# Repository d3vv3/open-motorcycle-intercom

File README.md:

<p align="center">
    
    <br/>
    <b>Open Source Mesh and Bluetooth Motorcycle Intercom</b>
    <br/>
    <br/>
    <a href="https://openhelmet.devve.space">website</a> | <a href="https://discord.gg/XxBSnwSDst">discord</a>
</p>

OpenHelmet is an **open-source, motorcycle intercom system**
designed to outperform current proprietary solutions in **latency, scalability, transparency, and hackability**.

## Key goals

- Open protocol and open firmware
- Commodity, off-the-shelf hardware
- Use any microphone and any speakers from your existing helmet setup
- Mesh networking for 4-8+ riders
- Real-time full-duplex voice
- 8-16 hours of active riding per charge
- Bluetooth phone and media audio (calls, GPS, music, etc)
- Interoperability with legacy Bluetooth intercoms (Cardo, Sena, etc.) via standard profiles

This project explicitly avoids reverse-engineering proprietary intercom protocols.
Interoperability is achieved **only through standard Bluetooth audio profiles**.

---

## Why

- Cardo/Sena mesh protocols are proprietary and closed
- True mesh interoperability with and between them is impossible today
- Voice communication requires **deterministic latency**, not best-effort networking

As a result, OpenHelmet is designed around **custom real-time audio transport**.

---

## Roadmap

### Single-MCU

See [the wiring guide](docs/wiring.md) for the ESP32-S31 Function CoreBoard-1.

- [x] **ESP32-S31 Function CoreBoard-1** with 16 MB flash and 16 MB PSRAM
- [x] Onboard ES8311 capture/codec and NS4150B/J9 output
- [x] TDMA mesh protocol over [ESP-NOW](https://www.espressif.com/en/solutions/low-power-solutions/esp-now) (2.4 GHz)
- [x] LC3 low-bitrate voice
- [x] Classic Bluetooth A2DP sink, AVRCP, and HFP HF client
- [x] VOX for voice activation
- [x] Configure ESP32 tx power to 20 dBm (100 mW) for ESP-NOW
- [x] Silence suppression - most silent audio frames are suppressed; control traffic and occasional comfort updates remain
- [x] Receive mixing with first-speaker retention; a new active source can replace the longest-silent source after 400 ms

Limitations:
- ESP-NOW is not interoperable with nRF52 ESB.
- The ESP-NOW and Bluetooth stacks share the same radio, so mesh and Bluetooth are mutually exclusive: turning mesh on turns Bluetooth off.

### Dual-MCU

Development and validation only. Check [the wiring guide](docs/wiring.md) for
the S31/nRF52840 SPI wiring.

The nRF52840 firmware uses the radio's +8 dBm output directly.
An nRF21540 is needed for additional range, efficiency and antenna radio distribution. See "Custom PCB" section below.

> The nRF21540 is needed for actual range improvements.
> The nRF52840 alone is not a range improvement over the ESP32-S31.

- [x] **ESP32-S31 + Nordic nRF52840**
- [x] TDMA mesh protocol over [ESB](https://docs.nordicsemi.com/bundle/ncs-latest/page/nrf/protocols/esb/index.html) radio with custom PHY control
  > ESB is configured for 2 Mbps with +8 dBm TX power
- [x] SPI audio & control bridge between MCUs
  > The nRF52840 is the SPI master and polls the ESP32 bridge every 2 ms.
- [x] Noise suppression path
- [ ] Allow user to choose between [ESP-NOW](https://www.espressif.com/en/solutions/low-power-solutions/esp-now) and [ESB](https://docs.nordicsemi.com/bundle/ncs-latest/page/nrf/protocols/esb/index.html)
  > ESP-NOW is not interoperable with nRF52 ESB. The firmware currently selects ESB when the bridge is detected and otherwise falls back to ESP-NOW; comparative range, power, and latency remain to be measured.
- [x] Relay grants limited to at most two active speakers
- [x] Three-source receive mixer with first-speaker retention and 400 ms silent-source eviction
- [x] Silence suppression - most silent audio frames are suppressed; control traffic and occasional comfort updates remain
- [x] Bluetooth media playback (music, GPS, etc.) during mesh operation.

### Custom PCB

- [x] Schematic
- [ ] PCB layout
- [x] Include [nRF21540 RF FEM](https://www.nordicsemi.com/Products/nRF21540) in the schematics and PCB design

See the [wiring guide](docs/wiring.md) for the current assembled prototype.

### Ongoing

- [x] Mute mesh during phone call; resume mesh after call ends
- [x] Mesh channels with RGB LED channel indicator by color (e.g. green=1, red=2, blue=3, etc.)
- [x] Buttons for channel selection, volume, mesh toggle, and Bluetooth pairing
- [x] Multi-hop mesh
- [x] Replace beeps with voice prompts for button operations
- [x] Hold prompts: holding a button announces what releasing it will do (mesh on/off, phone pairing, next channel)
- [x] Phone connect and disconnect beeps, and a "Phone paired" prompt after a new pairing
- [x] ESP-NOW mesh and Bluetooth take turns on the shared radio: mesh on turns Bluetooth off, mesh off turns it back on and reconnects the phone
- [ ] Power budgeting and optimization for 8-16 hours of active riding per charge
- [ ] Testing on real motorcycle rides
- [ ] E2EE

---

## Transport Protocol Design

### Why Not Bluetooth Mesh / BLE Audio

- High latency
- Unpredictable scheduling
- Poor scaling for continuous audio

These technologies are unsuitable for real-time group voice.

---

## Custom Mesh Strategy

### Scheduled Voice and Control

OpenHelmet divides each 20 ms TDMA frame into scheduled voice slots and a control window:

- **TDMA** for mesh audio packets
- A rotating owner for joined-node control traffic; coordinator SYNC frames have a reserved window
- Bounded randomized contention for unjoined ESP-NOW JOIN requests

#### TDMA (Voice)

Each current mesh audio payload represents 20 ms of sound: two 10 ms LC3 frames, encoded as 24 bytes each. These 48 bytes travel together in one packet, not in separate TDMA slots.

On the nRF transport, a bundle can also carry previous audio frames for loss recovery. This increases packet size without changing the 20 ms transmission cadence.

- Fixed time slots per node
- One bounded transmission opportunity per node per 20 ms TDMA frame
- Deadline checks reject work that is already late; they do not guarantee exact RF completion timing

Configured frame structure (20 ms frame, up to 8 nodes; durations include guard time):

```
| Slot 1 | Slot 2 | Slot 3 | ... | Slot 8 | Control | Margin |
|  2 ms  |  2 ms  |  2 ms  | ... |  2 ms  |   2 ms  |  2 ms |
```

- Voice slots: 8 × 2 ms = 16 ms
- Control window: 2 ms (scheduled sync/topology/status traffic)
- Frame margin: 2 ms
- Voice and control deadlines reserve the last 500 µs of each nominal 2 ms window, leaving 1.5 ms before the deadline

VOX suppresses local LC3 encoding and audio transmission during silence, after its hangover period. Capture and voice detection continue. The TDMA schedule remains unchanged, and synchronization, keepalives, and required relay/control traffic continue.

Motorcycle groups are small and topology changes slowly, making TDMA practical.

#### Control

Used for:
- Joining/leaving the group
- Topology updates
- Slot maps and synchronization

Joined-node control packets use a bounded queue and scheduled ownership. Unassigned ESP-NOW JOIN requests use a minimum interval plus randomized jitter. These rules reduce contention, but they do not guarantee collision-free RF operation.

---

## Quick Start

For published paired flash bundles and the alpha/stable release process, see
[Firmware releases](docs/releases.md).

### Prerequisites

- [ESP-IDF v6.1 preview](https://docs.espressif.com/projects/esp-idf/en/release-v6.1/esp32s31/get-started/)
- [ESP32-S31 Function CoreBoard-1](https://docs.espressif.com/projects/esp-idf/en/release-v6.1/esp32s31/get-started/) with 16 MB flash and 16 MB PSRAM
- ESP32-S31 support in ESP-IDF v6.1 is preview
- CI pins a tested ESP-IDF image that includes the upstream S31 Bluetooth
  sniff-subrate fix. The mutable `v6.1` tag does not contain that fix.
- (Optional) XIAO nRF52840
- USB-C data cables
- [Development environment and ESP32 setup](docs/getting_started.md)
- [Audio and dual-MCU wiring guide](docs/wiring.md)
- (Optional) [KiCad](https://www.kicad.org/)

### Build

```bash
# Optional local environment example (path is machine-specific; this installation
# may use the unpatched v6.1 image and does not include the S31 sniff-subrate fix)
source "$HOME/.espressif/tools/activate_idf_v6.1.sh"

# Select the ESP32-S31 preview target
idf.py --preview set-target esp32s31

# Build firmware
idf.py build
```

For the tested SDK image with the tested fix, use the same immutable image as CI
instead of a local v6.1 installation:

```bash
docker run --rm --user "$(id -u):$(id -g)" -e HOME=/tmp \
  -v "$PWD:/project" -w /project \
  espressif/idf@sha256:8ac794c57fd4cac246cb8d2ada4002fa26337ac7df683047b5b83743dbedb6b7 \
  bash -lc 'idf.py --preview set-target esp32s31 && idf.py build'
```

That image reports ESP-IDF commit `9a97f6c54ec638111ce55cd36581b3c192f15207`
and S31 Bluetooth binary commit `3d8cee57c4ccff603d4f52fe16be1f04ece78ede`;
the latter includes the upstream sniff-subrate fix. The stable `espressif/idf:v6.1`
tag does not include this fix. A delayed BOOT guard alone does not fix
phone-originated transitions: cooldown handling and the external Bluetooth
controller fix are also required.

For the optional XIAO nRF52840 firmware, build the Rust crate with its pinned toolchain and convert it to UF2
(see [getting started](docs/getting_started.md#build-the-nrf-firmware)):

```bash
(cd rust/nrf-embassy-firmware &&
  cargo build --locked --release --target thumbv7em-none-eabihf)

python3 tools/migration/nrf_proof.py \
  rust/nrf-embassy-firmware/target/thumbv7em-none-eabihf/release/nrf-embassy-firmware \
  rust/nrf-embassy-firmware/target/thumbv7em-none-eabihf/release/nrf-embassy-firmware.uf2
```

### Recovery and Flashing

```bash
# Find your serial port
ls /dev/ttyACM* /dev/ttyUSB*

# Native USB JTAG/OpenOCD with board/esp32s31-builtin.cfg is the validated
# recovery path on the current setup. Serial flashing has proved unreliable here.
```

### Monitor Serial Output

```bash
# Option 1: Using idf.py (interactive, requires TTY)
idf.py -p /dev/ttyACM0 monitor

# Option 2: Using stty + cat (non-interactive)
stty -F /dev/ttyACM0 115200 raw -echo && cat /dev/ttyACM0
```

**Exit monitor:** `Ctrl+]`

### Expected Boot Log

```
I (xxx) omi: ========================================
I (xxx) omi: OMI - Open Motorcycle Intercom
I (xxx) omi: Phase 2: Single-Hop RF Link
I (xxx) omi: ========================================
I (xxx) omi: Boot time: <milliseconds> ms
I (xxx) omi: IDF version: v6.1
I (xxx) omi: Free heap: <bytes> bytes
I (xxx) omi: ========================================
I (xxx) omi: nRF52840 not detected - using ESP-NOW transport
I (xxx) omi: Mesh networking ready (desired state: disabled)
I (xxx) omi: System running!
```

### Troubleshooting

| Issue | Solution |
|-------|----------|
| Device not found | Use a data cable (not charge-only), try different USB port |
| Garbage characters in monitor | Wrong baud rate, use 115200 |

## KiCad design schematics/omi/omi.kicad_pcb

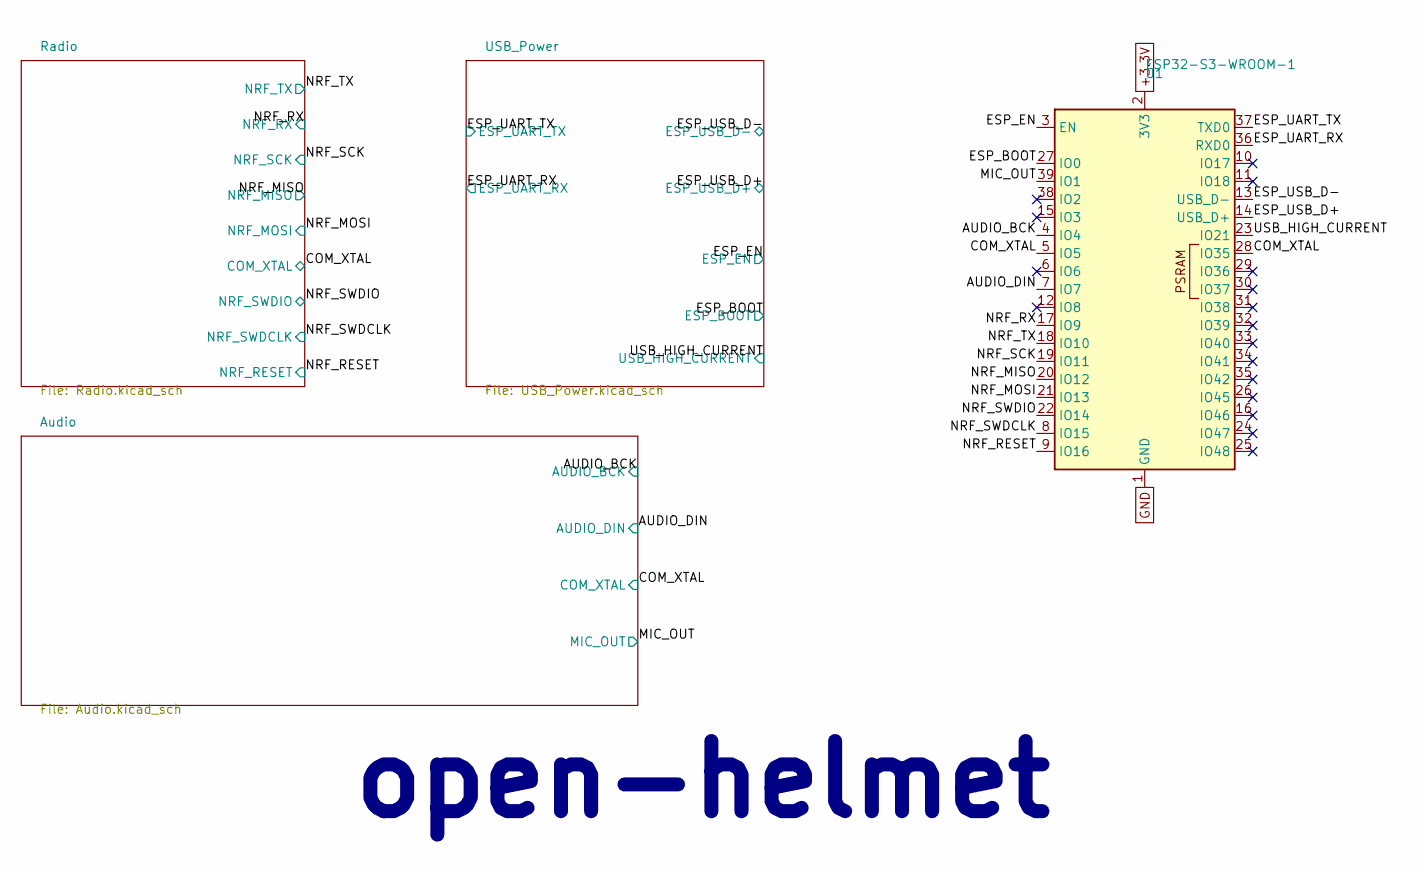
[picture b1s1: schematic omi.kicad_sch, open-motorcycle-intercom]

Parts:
U1: ESP32-S3-WROOM-1; MNF PART NUMBER ESP32-S3-WROOM-1-N8; LCSC C2913198

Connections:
+3.3V: U1.2 (3V3); also elsewhere on the board
/AUDIO_BCK: U1.4 (IO4); also elsewhere on the board
/AUDIO_DIN: U1.7 (IO7); also elsewhere on the board
/COM_XTAL: U1.5 (IO5), U1.28 (IO35); also elsewhere on the board
/ESP_BOOT: U1.27 (IO0); also elsewhere on the board
/ESP_EN: U1.3 (EN); also elsewhere on the board
/ESP_UART_RX: U1.36 (RXD0); also elsewhere on the board
/ESP_UART_TX: U1.37 (TXD0); also elsewhere on the board
/ESP_USB_D+: U1.14 (USB_D+); also elsewhere on the board
/ESP_USB_D-: U1.13 (USB_D-); also elsewhere on the board
/MIC_OUT: U1.39 (IO1); also elsewhere on the board
/NRF_MISO: U1.20 (IO12); also elsewhere on the board
/NRF_MOSI: U1.21 (IO13); also elsewhere on the board
/NRF_RESET: U1.9 (IO16); also elsewhere on the board
/NRF_RX: U1.17 (IO9); also elsewhere on the board
/NRF_SCK: U1.19 (IO11); also elsewhere on the board
/NRF_SWDCLK: U1.8 (IO15); also elsewhere on the board
/NRF_SWDIO: U1.22 (IO14); also elsewhere on the board
/NRF_TX: U1.18 (IO10); also elsewhere on the board
/USB_HIGH_CURRENT: U1.23 (IO21); also elsewhere on the board
GND: U1.1 (GND), U1.40 (GND), U1.41 (GND); also elsewhere on the board

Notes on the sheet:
open-helmet

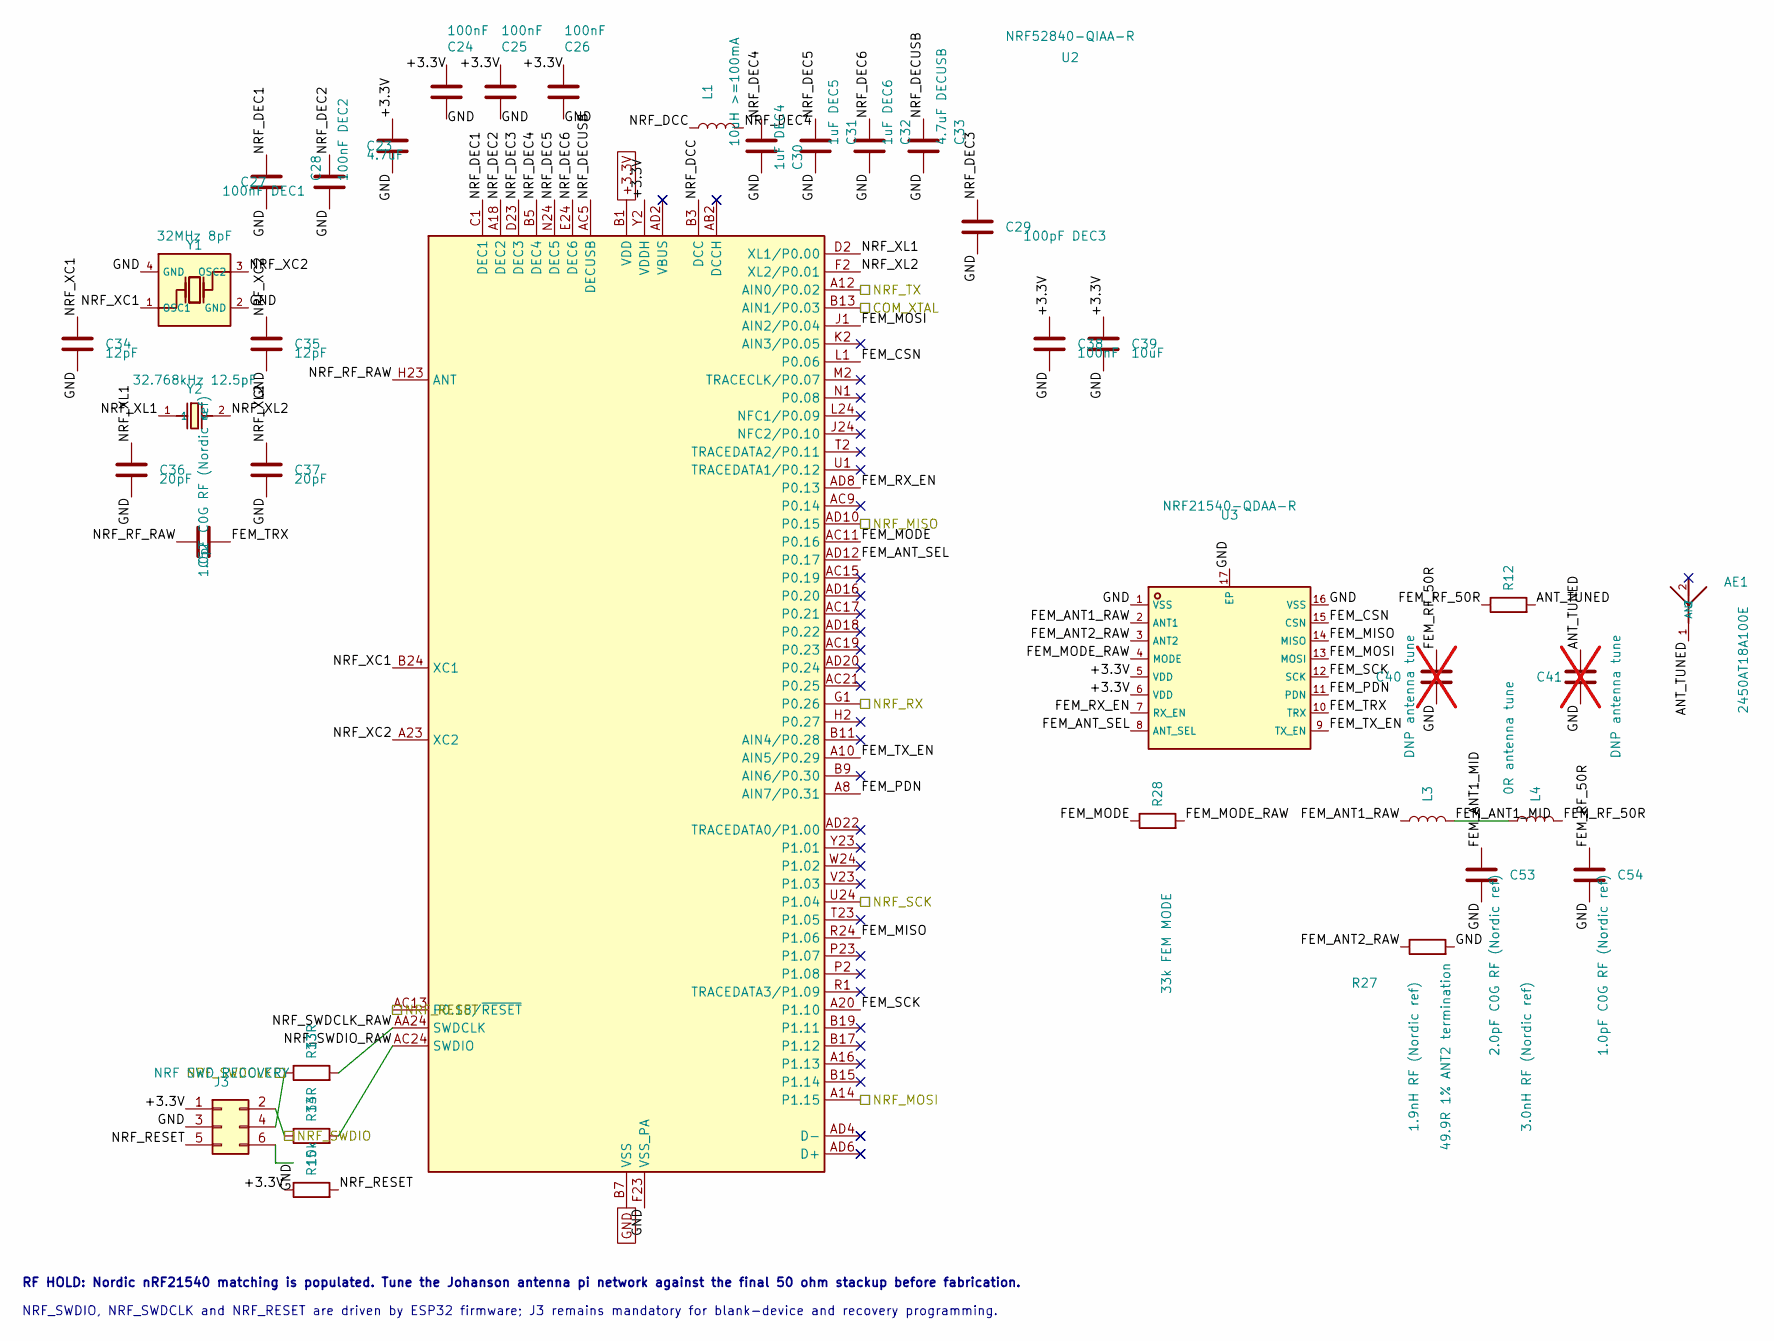
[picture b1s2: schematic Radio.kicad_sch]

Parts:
AE1: 2450AT18A100E; ANT-SMD_L3.2-W1.6; MNF PART NUMBER 2450AT18A100E; LCSC C89334
C23: 4.7uF; C_0805_2012Metric; MNF PART NUMBER C2012X7R1A475KT000N; LCSC C76639
C24, C25, C26, C38: 100nF; C_0603_1608Metric; MNF PART NUMBER CC0603KRX7R7BB104; LCSC C108079
C27: 100nF DEC1; C_0603_1608Metric; MNF PART NUMBER CC0603KRX7R7BB104; LCSC C108079
C28: 100nF DEC2; C_0603_1608Metric; MNF PART NUMBER CC0603KRX7R7BB104; LCSC C108079
C29: 100pF DEC3; C_0603_1608Metric; MNF PART NUMBER CC0603JRNPO9BN101; LCSC C14665
C30: 1uF DEC4; C_0603_1608Metric; MNF PART NUMBER CC0603KRX7R6BB105; LCSC C113807
C31: 1uF DEC5; C_0603_1608Metric; MNF PART NUMBER CC0603KRX7R6BB105; LCSC C113807
C32: 1uF DEC6; C_0603_1608Metric; MNF PART NUMBER CC0603KRX7R6BB105; LCSC C113807
C33: 4.7uF DECUSB; C_0805_2012Metric; MNF PART NUMBER C2012X7R1A475KT000N; LCSC C76639
C34, C35: 12pF; C_0603_1608Metric; MNF PART NUMBER CC0603JRNPO9BN120; LCSC C107034
C36, C37: 20pF; C_0603_1608Metric; MNF PART NUMBER CC0603GRNPO9BN200; LCSC C325469
C39: 10uF; C_0805_2012Metric; Voltage 10V; MNF PART NUMBER TCC0805X5R106K100FT; LCSC C380331
C40, C41: DNP antenna tune; C_0201_0603Metric; not fitted
C52, C54: 1.0pF C0G RF (Nordic ref); C_0201_0603Metric; MNF PART NUMBER GRM0335C1H1R0BA01D; LCSC C85893
C53: 2.0pF C0G RF (Nordic ref); C_0201_0603Metric; MNF PART NUMBER GJM0335C1E2R0BB01D; LCSC C88875
J3: NRF SWD RECOVERY; Tag-Connect_TC2030-IDC-NL_2x03_P1.27mm_Vertical; MNF PART NUMBER TC2030-IDC-NL; LCSC Not stocked - factory fixture
L1: 10uH >=100mA; L_0603_1608Metric; MNF PART NUMBER LQM18DN100M70L; LCSC C713281
L3: 1.9nH RF (Nordic ref); L_0201_0603Metric; MNF PART NUMBER LQP03TN1N9B02D; LCSC C206445
L4: 3.0nH RF (Nordic ref); L_0201_0603Metric; MNF PART NUMBER LQP03TN3N0B02D; LCSC C98044
R12: 0R antenna tune; R_0201_0603Metric; MNF PART NUMBER RC0201JR-070RL; LCSC C106228
R13, R14: 33R; R_0603_1608Metric; MNF PART NUMBER 0603WAF330JT5E; LCSC C23140
R15: 10k; R_0603_1608Metric; MNF PART NUMBER 0603WAF1002T5E; LCSC C25804
R27: 49.9R 1% ANT2 termination; R_0201_0603Metric; MNF PART NUMBER RC0201FR-0749R9L; LCSC C155744
R28: 33k FEM MODE; R_0603_1608Metric; MNF PART NUMBER 0603WAF3302T5E; LCSC C4216
U2: NRF52840-QIAA-R; AQFN-73_L7.0-W7.0-P0.50-BL-EP4.8; MNF PART NUMBER NRF52840-QIAA-R; LCSC C190794
U3: NRF21540-QDAA-R; QFN-16_L4.0-W4.0-P0.65-BL-EP2.7; MNF PART NUMBER NRF21540-QDAA-R; LCSC C1518188
Y1: 32MHz 8pF; CRYSTAL-SMD_4P-L3.2-W2.5-BL; MNF PART NUMBER S3232000081040; LCSC C426985
Y2: 32.768kHz 12.5pF; OSC-SMD_L3.2-W1.5; MNF PART NUMBER SC-32S32.768kHz20PPM12.5pF; LCSC C97606

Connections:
+3.3V: C23.1, C24.1, C25.1, C26.1, C38.1, C39.1, J3.1, R15.1, U2.A22 (VDD), U2.AD14 (VDD), U2.AD23 (VDD), U2.B1 (VDD), U2.W1 (VDD), U2.Y2 (VDDH), U3.5 (VDD), U3.6 (VDD); also elsewhere on the board
/COM_XTAL: U2.B13 (AIN1/P0.03); also elsewhere on the board
/NRF_MISO: U2.AD10 (P0.15); also elsewhere on the board
/NRF_MOSI: U2.A14 (P1.15); also elsewhere on the board
/NRF_RESET: J3.5, R15.2, U2.AC13 (P0.18/~RESET); also elsewhere on the board
/NRF_RX: U2.G1 (P0.26); also elsewhere on the board
/NRF_SCK: U2.U24 (P1.04); also elsewhere on the board
/NRF_SWDCLK: J3.4, R13.1; also elsewhere on the board
/NRF_SWDIO: J3.2, R14.1; also elsewhere on the board
/NRF_TX: U2.A12 (AIN0/P0.02); also elsewhere on the board
/Radio/ANT_TUNED: AE1.1 (ANT_1), C41.1, R12.2
/Radio/FEM_ANT1_MID: C53.1, L3.2, L4.1
/Radio/FEM_ANT1_RAW: L3.1, U3.2 (ANT1)
/Radio/FEM_ANT2_RAW: R27.1, U3.3 (ANT2)
/Radio/FEM_ANT_SEL: U2.AD12 (P0.17), U3.8 (ANT_SEL)
/Radio/FEM_CSN: U2.L1 (P0.06), U3.15 (CSN)
/Radio/FEM_MISO: U2.R24 (P1.06), U3.14 (MISO)
/Radio/FEM_MODE: R28.1, U2.AC11 (P0.16)
/Radio/FEM_MODE_RAW: R28.2, U3.4 (MODE)
/Radio/FEM_MOSI: U2.J1 (AIN2/P0.04), U3.13 (MOSI)
/Radio/FEM_PDN: U2.A8 (AIN7/P0.31), U3.11 (PDN)
/Radio/FEM_RF_50R: C40.1, C54.1, L4.2, R12.1
/Radio/FEM_RX_EN: U2.AD8 (P0.13), U3.7 (RX_EN)
/Radio/FEM_SCK: U2.A20 (P1.10), U3.12 (SCK)
/Radio/FEM_TRX: C52.2, U3.10 (TRX)
/Radio/FEM_TX_EN: U2.A10 (AIN5/P0.29), U3.9 (TX_EN)
/Radio/NRF_DCC: L1.1, U2.B3 (DCC)
/Radio/NRF_DEC1: C27.1, U2.C1 (DEC1)
/Radio/NRF_DEC2: C28.1, U2.A18 (DEC2)
/Radio/NRF_DEC3: C29.1, U2.D23 (DEC3)
/Radio/NRF_DEC4: C30.1, L1.2, U2.B5 (DEC4)
/Radio/NRF_DEC5: C31.1, U2.N24 (DEC5)
/Radio/NRF_DEC6: C32.1, U2.E24 (DEC6)
/Radio/NRF_DECUSB: C33.1, U2.AC5 (DECUSB)
/Radio/NRF_RF_RAW: C52.1, U2.H23 (ANT)
/Radio/NRF_SWDCLK_RAW: R13.2, U2.AA24 (SWDCLK)
/Radio/NRF_SWDIO_RAW: R14.2, U2.AC24 (SWDIO)
/Radio/NRF_XC1: C34.1, U2.B24 (XC1), Y1.1 (OSC1)
/Radio/NRF_XC2: C35.1, U2.A23 (XC2), Y1.3 (OSC2)
/Radio/NRF_XL1: C36.1, U2.D2 (XL1/P0.00), Y2.1
/Radio/NRF_XL2: C37.1, U2.F2 (XL2/P0.01), Y2.2
GND: C23.2, C24.2, C25.2, C26.2, C27.2, C28.2, C29.2, C30.2, C31.2, C32.2, C33.2, C34.2, C35.2, C36.2, C37.2, C38.2, C39.2, C40.2, C41.2, C53.2, C54.2, J3.3, J3.6, R27.2, U2.B7 (VSS), U2.EP (VSS), U2.F23 (VSS_PA), U3.1 (VSS), U3.16 (VSS), U3.17 (EP), Y1.2 (GND), Y1.4 (GND); also elsewhere on the board

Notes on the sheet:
RF HOLD: Nordic nRF21540 matching is populated. Tune the Johanson antenna pi network against the final 50 ohm stackup before fabrication.
NRF_SWDIO, NRF_SWDCLK and NRF_RESET are driven by ESP32 firmware; J3 remains mandatory for blank-device and recovery programming.

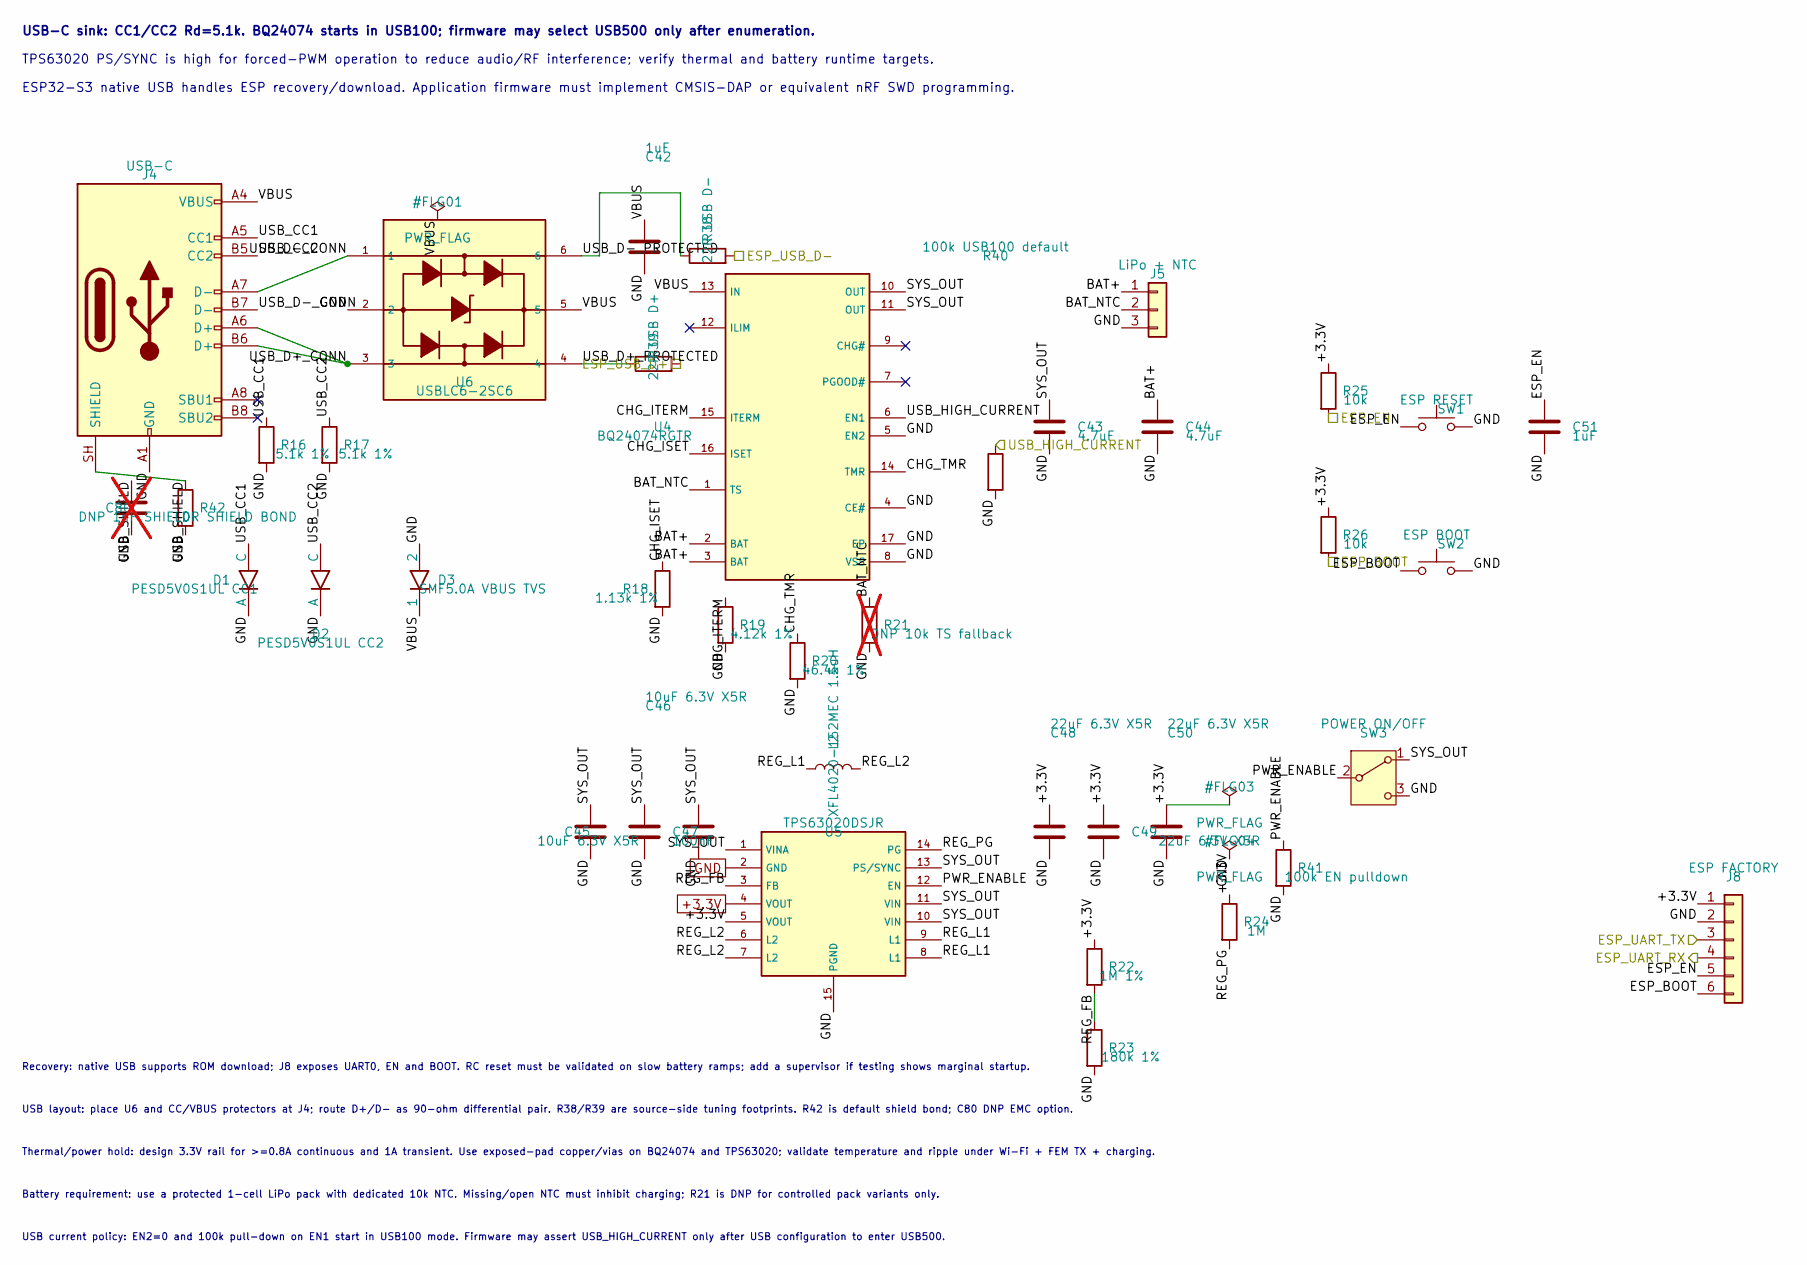
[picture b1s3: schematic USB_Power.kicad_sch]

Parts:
C42, C51: 1uF; C_0603_1608Metric; MNF PART NUMBER CC0603KRX7R6BB105; LCSC C113807
C43, C44: 4.7uF; C_0805_2012Metric; MNF PART NUMBER C2012X7R1A475KT000N; LCSC C76639
C45, C46: 10uF 6.3V X5R; C_0805_2012Metric; MNF PART NUMBER TCC0805X5R106K100FT; LCSC C380331
C47: 100nF; C_0603_1608Metric; MNF PART NUMBER CC0603KRX7R7BB104; LCSC C108079
C48, C49, C50: 22uF 6.3V X5R; C_0805_2012Metric; MNF PART NUMBER TCC0805X5R226K100FT; LCSC C380336
C80: DNP 1nF SHIELD; C_0603_1608Metric; MNF PART NUMBER TBD EMC tuning; not fitted
D1: PESD5V0S1UL CC1; SOD-882_L1.0-W0.6-RD; MNF PART NUMBER PESD5V0S1UL,315; LCSC C85402
D2: PESD5V0S1UL CC2; SOD-882_L1.0-W0.6-RD; MNF PART NUMBER PESD5V0S1UL,315; LCSC C85402
D3: SMF5.0A VBUS TVS; SOD-123F_L2.8-W1.8-LS3.7-RD; MNF PART NUMBER SMF5.0A; LCSC C151296
J4: USB-C; USB_C_Receptacle_HRO_TYPE-C-31-M-12; MNF PART NUMBER TYPE-C-31-M-12; LCSC C165948
J5: LiPo + NTC; JST_GH_BM03B-GHS-TBT_1x03-1MP_P1.25mm_Vertical; MNF PART NUMBER BM03B-GHS-TBT(LF)(SN); LCSC C161691
J8: ESP FACTORY; PinHeader_1x06_P2.54mm_Vertical; MNF PART NUMBER PZ254V-11-06P; LCSC C492405
L2: XFL4020-152MEC 1.5uH; IND-SMD_L4.0-W4.0-A; MNF PART NUMBER XFL4020-152MEC; LCSC C3033018
R16, R17: 5.1k 1%; R_0603_1608Metric; MNF PART NUMBER 0603WAF5101T5E; LCSC C23186
R18: 1.13k 1%; R_0603_1608Metric; MNF PART NUMBER 0603WAF1131T5E; LCSC C22833
R19: 4.12k 1%; R_0603_1608Metric; MNF PART NUMBER 0603WAF4121T5E; LCSC C23041
R20: 46.4k 1%; R_0603_1608Metric; MNF PART NUMBER 0603WAF4642T5E; LCSC C23059
R21: DNP 10k TS fallback; R_0603_1608Metric; MNF PART NUMBER 0603WAF1002T5E; LCSC C25804; not fitted
R22: 1M 1%; R_0603_1608Metric; MNF PART NUMBER 0603WAF1004T5E; LCSC C22935
R23: 180k 1%; R_0603_1608Metric; MNF PART NUMBER 0603WAF1803T5E; LCSC C22827
R24: 1M; R_0603_1608Metric; MNF PART NUMBER 0603WAF1004T5E; LCSC C22935
R25, R26: 10k; R_0603_1608Metric; MNF PART NUMBER 0603WAF1002T5E; LCSC C25804
R38: 22R USB D-; R_0603_1608Metric; MNF PART NUMBER 0603WAF220JT5E; LCSC C23345
R39: 22R USB D+; R_0603_1608Metric; MNF PART NUMBER 0603WAF220JT5E; LCSC C23345
R40: 100k USB100 default; R_0603_1608Metric; MNF PART NUMBER 0603WAF1003T5E; LCSC C25803
R41: 100k EN pulldown; R_0603_1608Metric; MNF PART NUMBER 0603WAF1003T5E; LCSC C25803
R42: 0R SHIELD BOND; R_0603_1608Metric; MNF PART NUMBER 0603WAF0000T5E; LCSC C21189
SW1: ESP RESET; SW_Push_1P1T_XKB_TS-1187A; MNF PART NUMBER TS-1187A-B-A-B; LCSC C318884
SW2: ESP BOOT; SW_Push_1P1T_XKB_TS-1187A; MNF PART NUMBER TS-1187A-B-A-B; LCSC C318884
SW3: POWER ON/OFF; SW_SPDT_Shouhan_MSK12C02; MNF PART NUMBER MSK12C02; LCSC C431540
U4: BQ24074RGTR; QFN-16_L3.0-W3.0-P0.50-TL-EP1.7; MNF PART NUMBER BQ24074RGTR; LCSC C54313
U5: TPS63020DSJR; VSON-14_L4.0-W3.0-P0.50-BL-EP_TI_DSJ; MNF PART NUMBER TPS63020DSJR; LCSC C15483
U6: USBLC6-2SC6; SOT-23-6_L2.9-W1.6-P0.95-LS2.8-BL; MNF PART NUMBER TYPE-C-31-M-12; LCSC C7519

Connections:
+3.3V: C48.1, C49.1, C50.1, J8.1, R22.1, R24.1, R25.1, R26.1, U5.4 (VOUT), U5.5 (VOUT); also elsewhere on the board
/ESP_BOOT: J8.6, R26.2, SW2.1; also elsewhere on the board
/ESP_EN: C51.1, J8.5, R25.2, SW1.1; also elsewhere on the board
/ESP_UART_RX: J8.4; also elsewhere on the board
/ESP_UART_TX: J8.3; also elsewhere on the board
/ESP_USB_D+: R39.2; also elsewhere on the board
/ESP_USB_D-: R38.2; also elsewhere on the board
/USB_HIGH_CURRENT: R40.1, U4.6 (EN1); also elsewhere on the board
/USB_Power/BAT+: C44.1, J5.1, U4.2 (BAT), U4.3 (BAT)
/USB_Power/BAT_NTC: J5.2, R21.1, U4.1 (TS)
/USB_Power/CHG_ISET: R18.1, U4.16 (ISET)
/USB_Power/CHG_ITERM: R19.1, U4.15 (ITERM)
/USB_Power/CHG_TMR: R20.1, U4.14 (TMR)
/USB_Power/PWR_ENABLE: R41.1, SW3.2 (B), U5.12 (EN)
/USB_Power/REG_FB: R22.2, R23.1, U5.3 (FB)
/USB_Power/REG_L1: L2.1, U5.8 (L1), U5.9 (L1)
/USB_Power/REG_L2: L2.2, U5.6 (L2), U5.7 (L2)
/USB_Power/REG_PG: R24.2, U5.14 (PG)
/USB_Power/SYS_OUT: C43.1, C45.1, C46.1, C47.1, SW3.1 (A), U4.10 (OUT), U4.11 (OUT), U5.1 (VINA), U5.10 (VIN), U5.11 (VIN), U5.13 (PS/SYNC)
/USB_Power/USB_CC1: D1.1 (C), J4.A5 (CC1), R16.1
/USB_Power/USB_CC2: D2.1 (C), J4.B5 (CC2), R17.1
/USB_Power/USB_D+_CONN: J4.A6 (D+), J4.B6 (D+), U6.3
/USB_Power/USB_D+_PROTECTED: R39.1, U6.4
/USB_Power/USB_D-_CONN: J4.A7 (D-), J4.B7 (D-), U6.1
/USB_Power/USB_D-_PROTECTED: R38.1, U6.6
/USB_Power/USB_SHIELD: C80.1, J4.SH (SHIELD), R42.1
/USB_Power/VBUS: C42.1, D3.1, J4.A4 (VBUS), J4.A9 (VBUS), J4.B4 (VBUS), J4.B9 (VBUS), U4.13 (IN), U6.5
GND: C42.2, C43.2, C44.2, C45.2, C46.2, C47.2, C48.2, C49.2, C50.2, C51.2, C80.2, D1.2 (A), D2.2 (A), D3.2, J4.A1 (GND), J4.A12 (GND), J4.B1 (GND), J4.B12 (GND), J5.3, J8.2, R16.2, R17.2, R18.2, R19.2, R20.2, R21.2, R23.2, R40.2, R41.2, R42.2, SW1.2, SW2.2, SW3.3 (C), U4.4 (CE#), U4.5 (EN2), U4.8 (VSS), U4.17 (EP), U5.2 (GND), U5.15 (PGND), U6.2; also elsewhere on the board

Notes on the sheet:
USB-C sink: CC1/CC2 Rd=5.1k. BQ24074 starts in USB100; firmware may select USB500 only after enumeration.
TPS63020 PS/SYNC is high for forced-PWM operation to reduce audio/RF interference; verify thermal and battery runtime targets.
ESP32-S3 native USB handles ESP recovery/download. Application firmware must implement CMSIS-DAP or equivalent nRF SWD programming.
USB current policy: EN2=0 and 100k pull-down on EN1 start in USB100 mode. Firmware may assert USB_HIGH_CURRENT only after USB configuration to enter USB500.
Battery requirement: use a protected 1-cell LiPo pack with dedicated 10k NTC. Missing/open NTC must inhibit charging; R21 is DNP for controlled pack variants only.
Thermal/power hold: design 3.3V rail for >=0.8A continuous and 1A transient. Use exposed-pad copper/vias on BQ24074 and TPS63020; validate temperature and ripple under Wi-Fi + FEM TX + charging.
USB layout: place U6 and CC/VBUS protectors at J4; route D+/D- as 90-ohm differential pair. R38/R39 are source-side tuning footprints. R42 is default shield bond; C80 DNP EMC option.
Recovery: native USB supports ROM download; J8 exposes UART0, EN and BOOT. RC reset must be validated on slow battery ramps; add a supervisor if testing shows marginal startup.

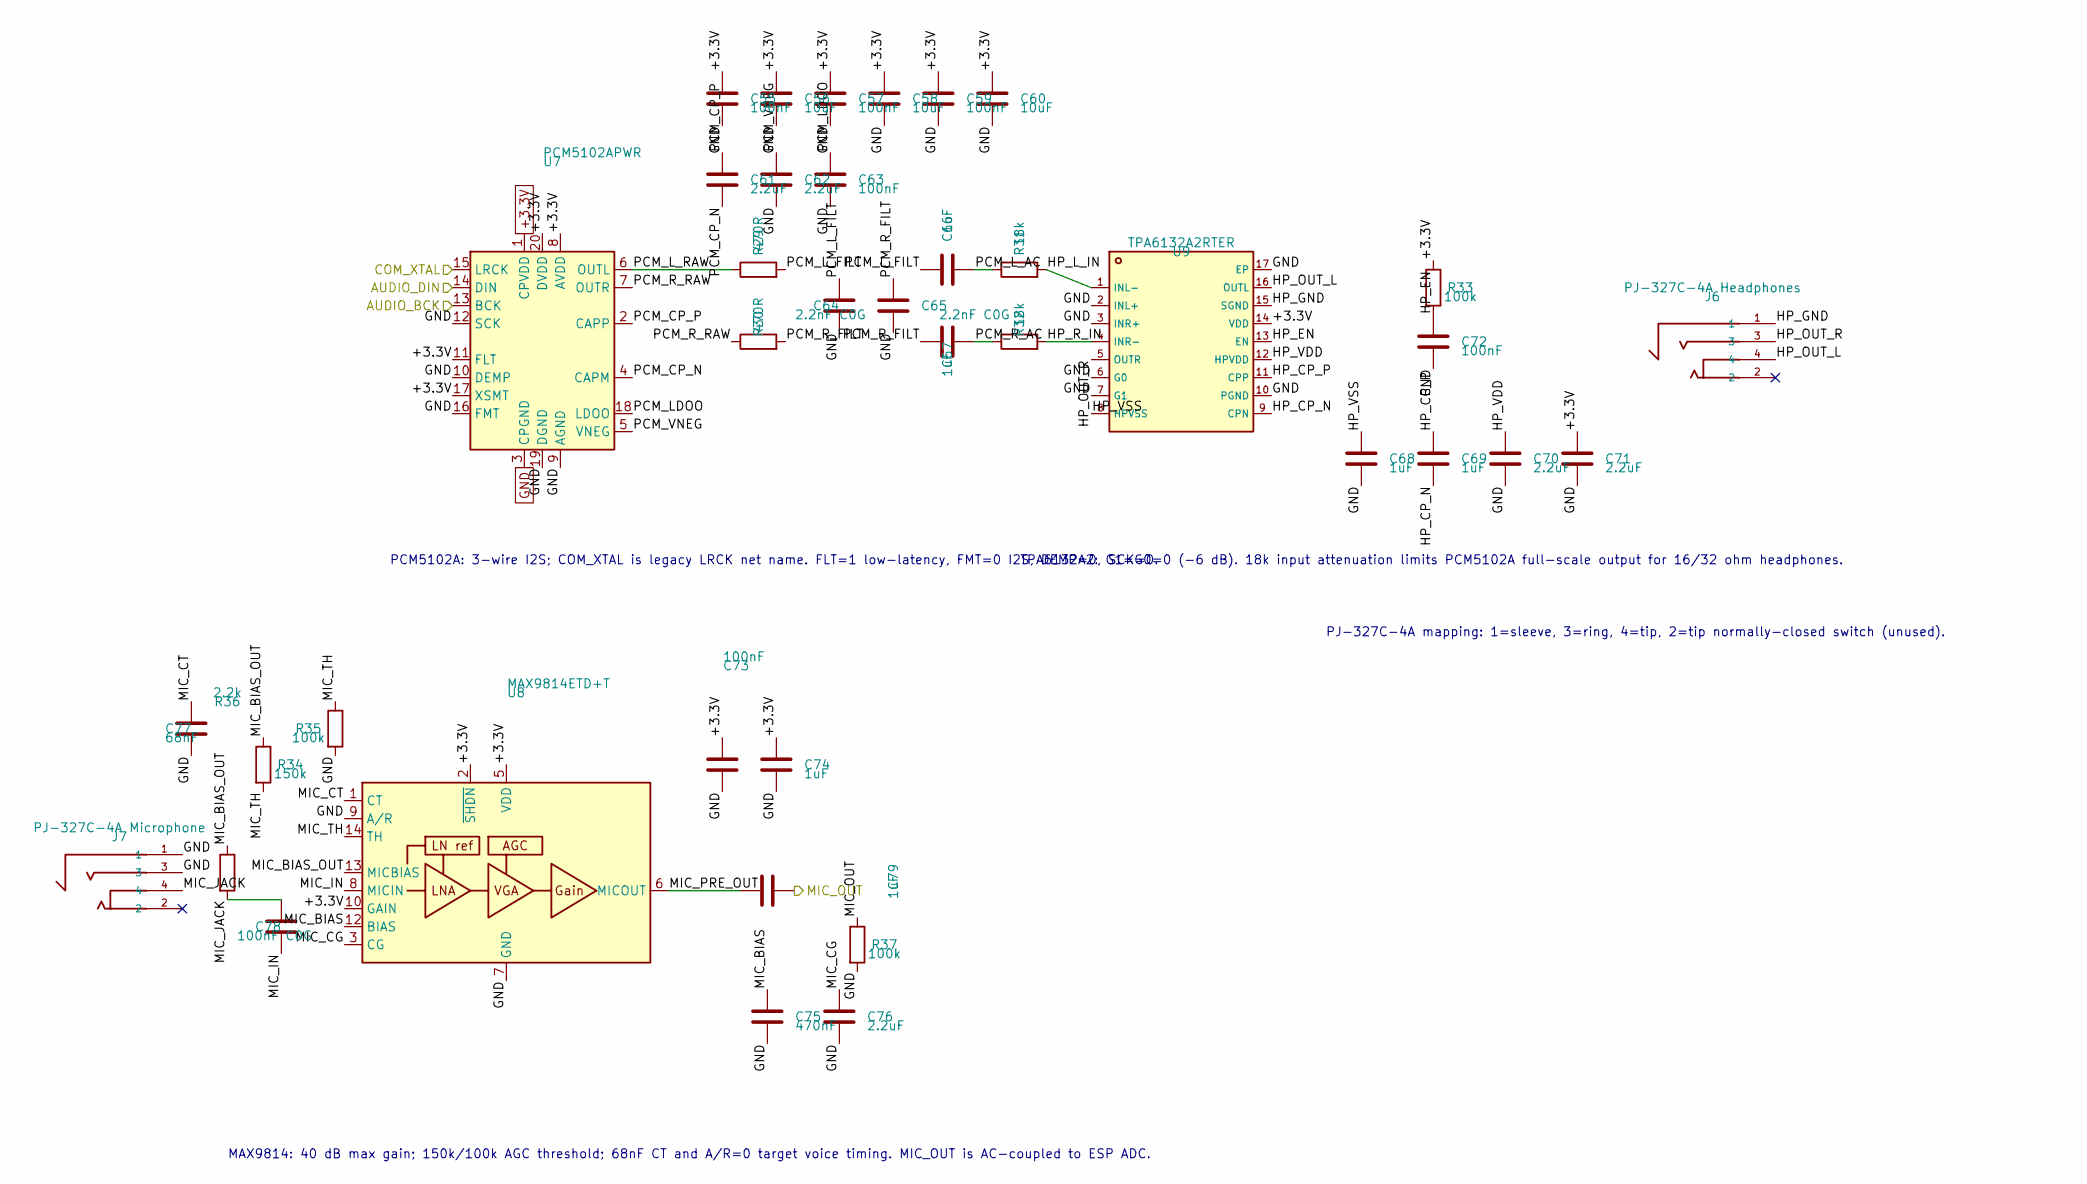
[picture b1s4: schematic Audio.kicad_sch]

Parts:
C55, C57, C59, C63, C72, C73: 100nF; C_0603_1608Metric; MNF PART NUMBER CC0603KRX7R7BB104; LCSC C108079
C56, C58, C60: 10uF; C_0805_2012Metric; MNF PART NUMBER TCC0805X5R106K100FT; LCSC C380331
C61, C62, C70, C71, C76: 2.2uF; C_0603_1608Metric; MNF PART NUMBER CC0603KRX7R6BB225; LCSC C513691
C64, C65: 2.2nF C0G; C_0603_1608Metric; MNF PART NUMBER CC0603JRNPO9BN222; LCSC C107043
C66, C67, C68, C69, C74, C79: 1uF; C_0603_1608Metric; MNF PART NUMBER CC0603KRX7R6BB105; LCSC C113807
C75: 470nF; C_0603_1608Metric; MNF PART NUMBER CC0603KRX7R7BB474; LCSC C1623
C77: 68nF; C_0603_1608Metric; MNF PART NUMBER CC0603KRX7R8BB683; LCSC C107071
C78: 100nF C0G; C_1206_3216Metric; MNF PART NUMBER 1206N104J500CT; LCSC C170182
J6: PJ-327C-4A Headphones; AUDIO-SMD_PJ-327C-4A; MNF PART NUMBER PJ-327C-4A; LCSC C145813
J7: PJ-327C-4A Microphone; AUDIO-SMD_PJ-327C-4A; MNF PART NUMBER PJ-327C-4A; LCSC C145813
R29, R30: 470R; R_0603_1608Metric; MNF PART NUMBER 0603WAF4700T5E; LCSC C23179
R31, R32: 18k; R_0603_1608Metric; MNF PART NUMBER 0603WAF1802T5E; LCSC C25810
R33, R35, R37: 100k; R_0603_1608Metric; MNF PART NUMBER 0603WAF1003T5E; LCSC C25803
R34: 150k; R_0603_1608Metric; MNF PART NUMBER 0603WAF1503T5E; LCSC C22807
R36: 2.2k; R_0603_1608Metric; MNF PART NUMBER 0603WAF2201T5E; LCSC C4190
U7: PCM5102APWR; TSSOP-20_L6.5-W4.4-P0.65-LS6.4-BL; MNF PART NUMBER PCM5102APWR; LCSC C107671
U8: MAX9814ETD+T; TDFN-14_L3.0-W3.0-P0.40-BL-EP; MNF PART NUMBER MAX9814ETD+T; LCSC C41714
U9: TPA6132A2RTER; WQFN-16_L3.0-W3.0-P0.50-TL-EP1.6; MNF PART NUMBER TPA6132A2RTER; LCSC C69901

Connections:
+3.3V: C55.1, C56.1, C57.1, C58.1, C59.1, C60.1, C71.1, C73.1, C74.1, R33.1, U7.1 (CPVDD), U7.8 (AVDD), U7.11 (FLT), U7.17 (XSMT), U7.20 (DVDD), U8.2 (~SHDN), U8.5 (VDD), U8.10 (GAIN), U9.14 (VDD); also elsewhere on the board
/AUDIO_BCK: U7.13 (BCK); also elsewhere on the board
/AUDIO_DIN: U7.14 (DIN); also elsewhere on the board
/Audio/HP_CP_N: C69.2, U9.9 (CPN)
/Audio/HP_CP_P: C69.1, U9.11 (CPP)
/Audio/HP_EN: C72.1, R33.2, U9.13 (EN)
/Audio/HP_GND: J6.1, U9.15 (SGND)
/Audio/HP_L_IN: R31.2, U9.1 (INL-)
/Audio/HP_OUT_L: J6.4, U9.16 (OUTL)
/Audio/HP_OUT_R: J6.3, U9.5 (OUTR)
/Audio/HP_R_IN: R32.2, U9.4 (INR-)
/Audio/HP_VDD: C70.1, U9.12 (HPVDD)
/Audio/HP_VSS: C68.1, U9.8 (HPVSS)
/Audio/MIC_BIAS: C75.1, U8.12 (BIAS)
/Audio/MIC_BIAS_OUT: R34.1, R36.1, U8.13 (MICBIAS)
/Audio/MIC_CG: C76.1, U8.3 (CG)
/Audio/MIC_CT: C77.1, U8.1 (CT)
/Audio/MIC_IN: C78.2, U8.8 (MICIN)
/Audio/MIC_JACK: C78.1, J7.4, R36.2
/Audio/MIC_PRE_OUT: C79.1, U8.6 (MICOUT)
/Audio/MIC_TH: R34.2, R35.1, U8.14 (TH)
/Audio/PCM_CP_N: C61.2, U7.4 (CAPM)
/Audio/PCM_CP_P: C61.1, U7.2 (CAPP)
/Audio/PCM_LDOO: C63.1, U7.18 (LDOO)
/Audio/PCM_L_AC: C66.2, R31.1
/Audio/PCM_L_FILT: C64.1, C66.1, R29.2
/Audio/PCM_L_RAW: R29.1, U7.6 (OUTL)
/Audio/PCM_R_AC: C67.2, R32.1
/Audio/PCM_R_FILT: C65.1, C67.1, R30.2
/Audio/PCM_R_RAW: R30.1, U7.7 (OUTR)
/Audio/PCM_VNEG: C62.1, U7.5 (VNEG)
/COM_XTAL: U7.15 (LRCK); also elsewhere on the board
/MIC_OUT: C79.2, R37.1; also elsewhere on the board
GND: C55.2, C56.2, C57.2, C58.2, C59.2, C60.2, C62.2, C63.2, C64.2, C65.2, C68.2, C70.2, C71.2, C72.2, C73.2, C74.2, C75.2, C76.2, C77.2, J7.1, J7.3, R35.2, R37.2, U7.3 (CPGND), U7.9 (AGND), U7.10 (DEMP), U7.12 (SCK), U7.16 (FMT), U7.19 (DGND), U8.4 (GND), U8.7 (GND), U8.9 (A/R), U8.11 (GND), U8.15 (GND), U9.2 (INL+), U9.3 (INR+), U9.6 (G0), U9.7 (G1), U9.10 (PGND), U9.17 (EP); also elsewhere on the board

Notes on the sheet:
PCM5102A: 3-wire I2S; COM_XTAL is legacy LRCK net name. FLT=1 low-latency, FMT=0 I2S, DEMP=0, SCK=0.
TPA6132A2: G1=G0=0 (-6 dB). 18k input attenuation limits PCM5102A full-scale output for 16/32 ohm headphones.
PJ-327C-4A mapping: 1=sleeve, 3=ring, 4=tip, 2=tip normally-closed switch (unused).
MAX9814: 40 dB max gain; 150k/100k AGC threshold; 68nF CT and A/R=0 target voice timing. MIC_OUT is AC-coupled to ESP ADC.
